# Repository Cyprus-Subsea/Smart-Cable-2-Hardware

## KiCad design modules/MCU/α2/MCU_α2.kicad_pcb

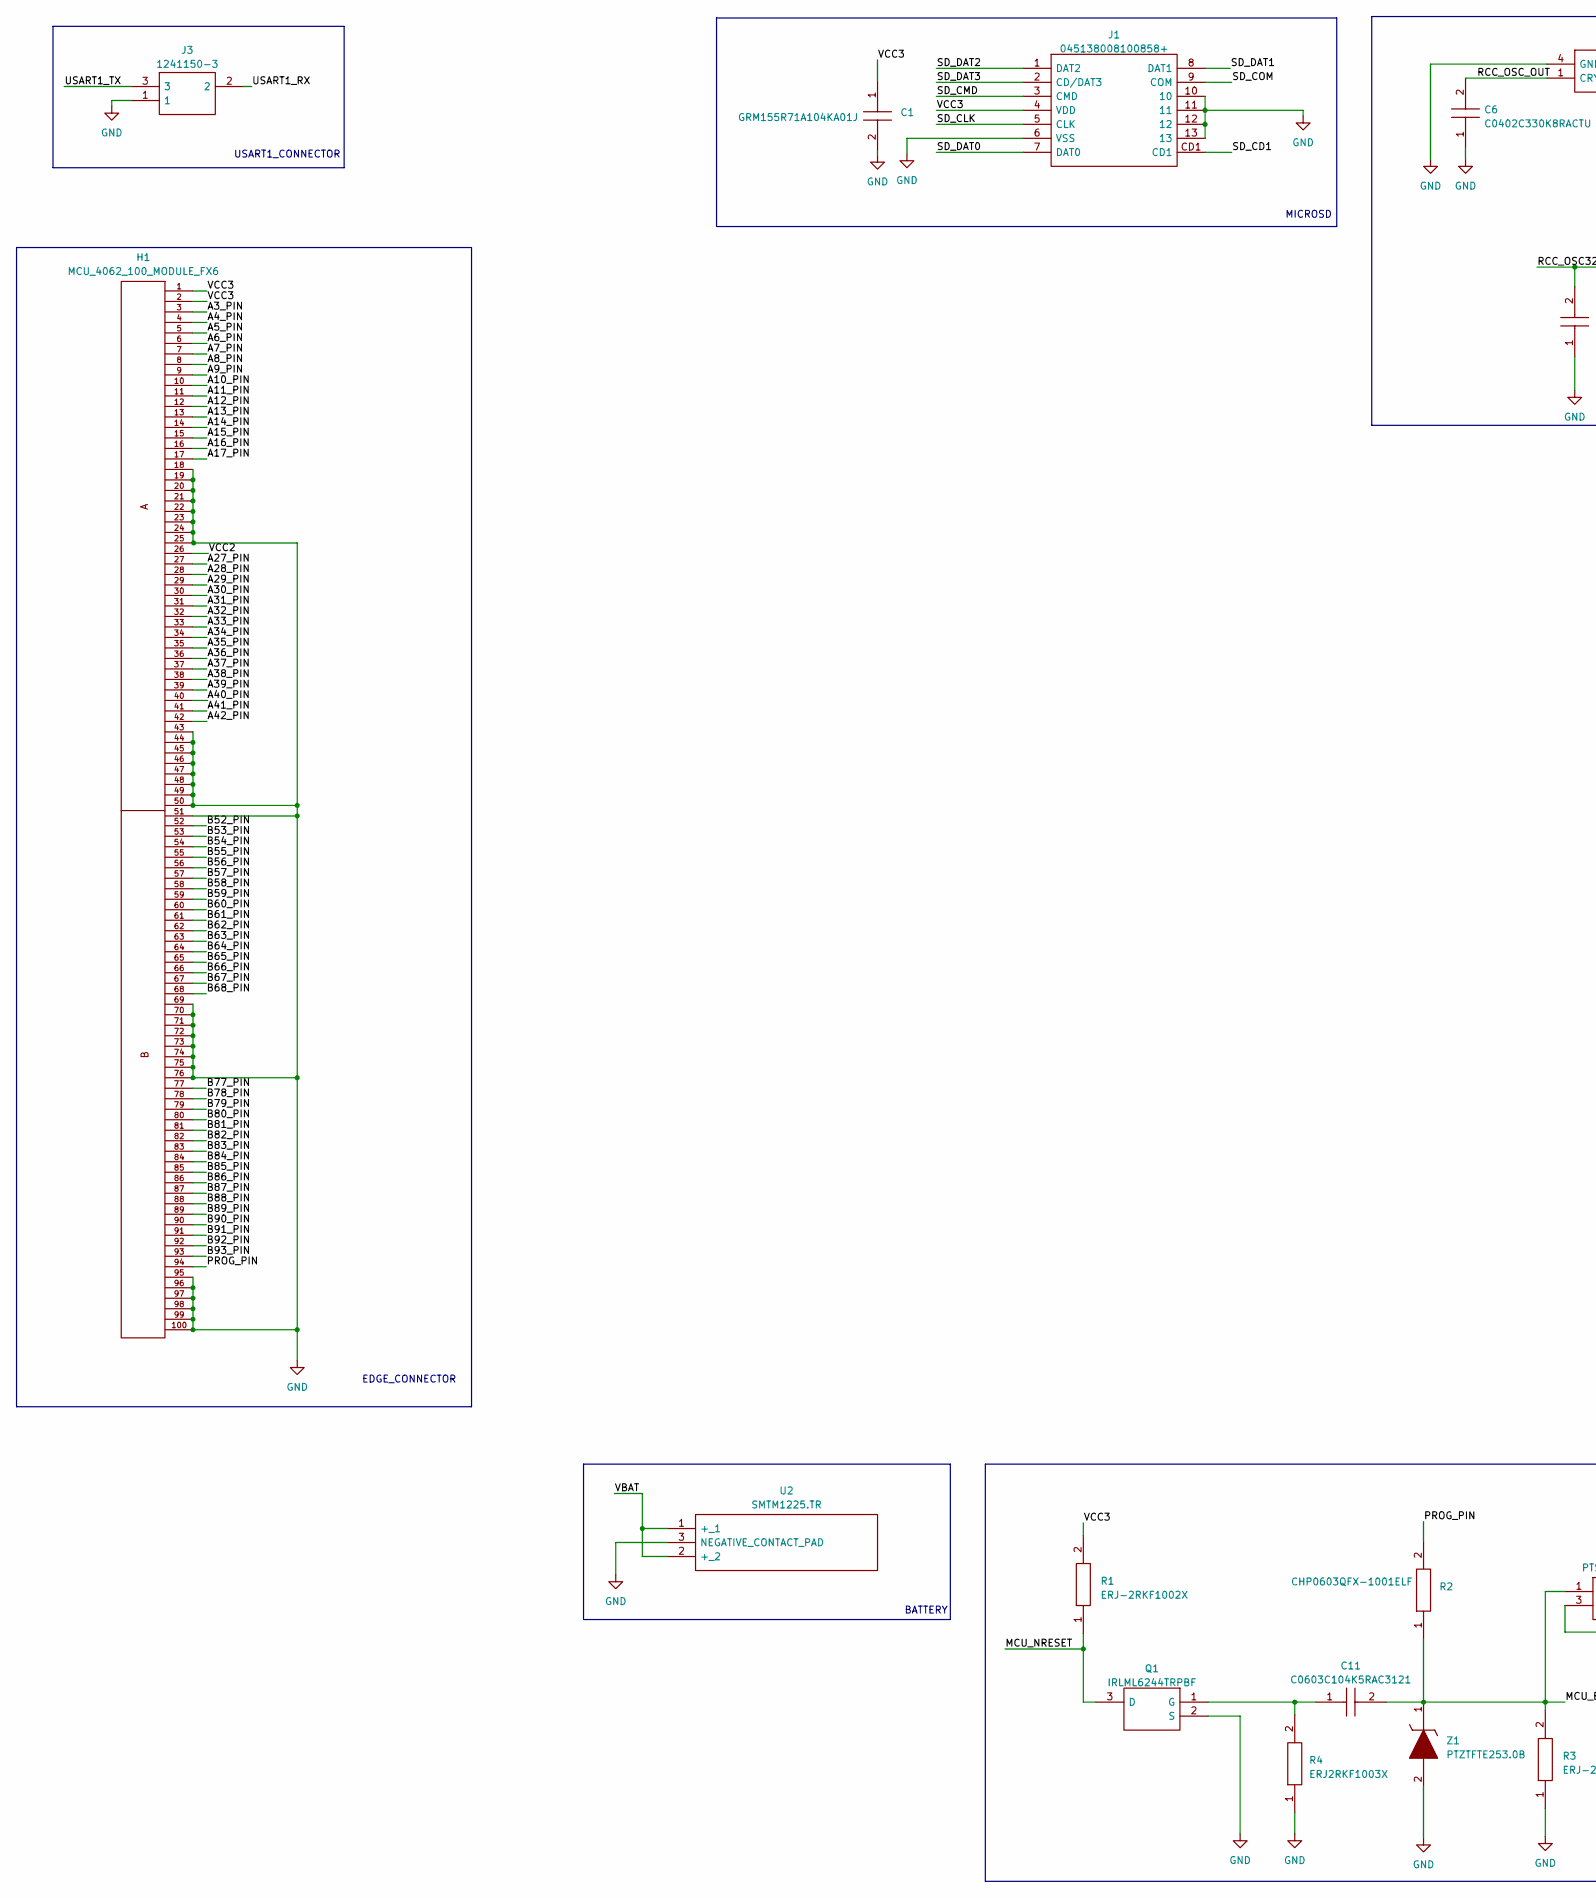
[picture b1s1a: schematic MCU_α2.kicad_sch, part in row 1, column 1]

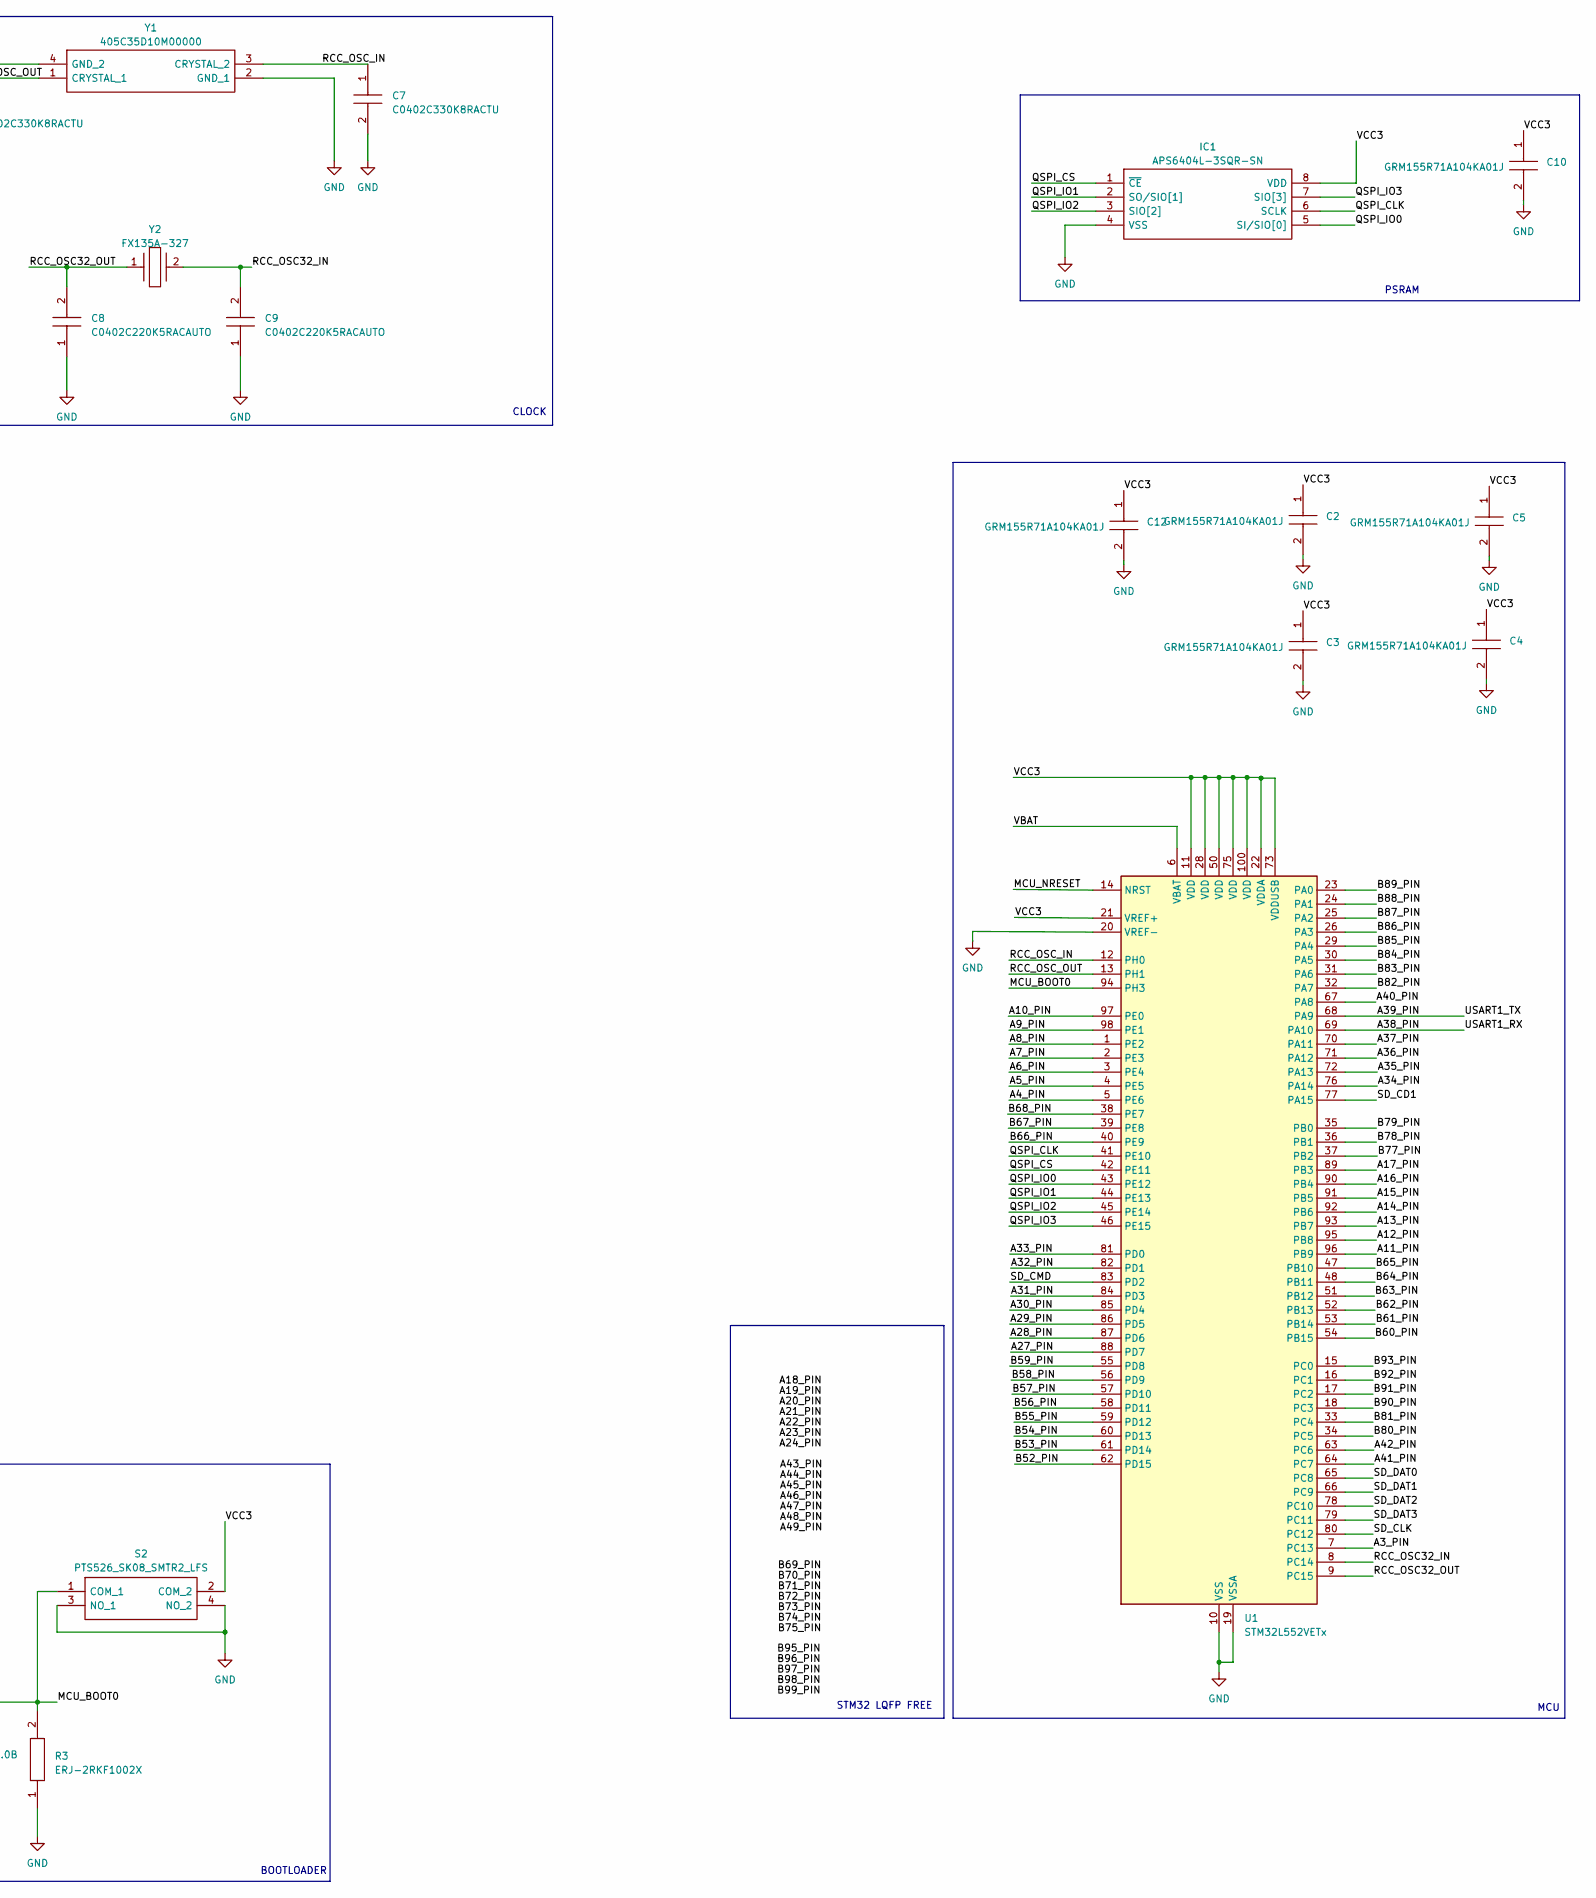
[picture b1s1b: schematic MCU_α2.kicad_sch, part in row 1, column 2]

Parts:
C1, C2, C3, C4, C5, C10, C12: GRM155R71A104KA01J; CAPC1005X55N; Manufacturer_Part_Number GRM155R71A104KA01J; Mouser Part Number 81-GRM155R71A104KA1J
C6, C7: C0402C330K8RACTU; CAPC1005X55N; Manufacturer_Part_Number C0402C330K8RACTU; Mouser Part Number 80-C0402C330K8RACTU
C8, C9: C0402C220K5RACAUTO; C0402; Manufacturer_Part_Number C0402C220K5RACAUTO; Mouser Part Number 80-C0402C220K5RAUTO
C11: C0603C104K5RAC3121; CAPC1608X95N; Manufacturer_Part_Number C0603C104K5RAC3121; Mouser Part Number 80-C603C104K5RAC3121
H1: MCU_4062_100_MODULE_FX6
IC1: APS6404L-3SQR-SN; SOIC127P600X175-8N; Manufacturer_Part_Number APS6404L-3SQR-SN; Mouser Part Number 878-APS6404L-3SQR-SN
J1: 045138008100858+; 045138008100858; Manufacturer_Part_Number 045138008100858+; Mouser Part Number 581-045138008100858+
J3: 1241150-3; 12411503; Manufacturer_Part_Number 1241150-3; Mouser Part Number 571-1241150-3
Q1: IRLML6244TRPBF; SOT95P237X112-3N; Manufacturer_Part_Number IRLML6244TRPBF; Mouser Part Number 942-IRLML6244TRPBF
R1, R3: ERJ-2RKF1002X; ERJ2RKD1004X; Manufacturer_Part_Number ERJ-2RKF1002X; Mouser Part Number 667-ERJ-2RKF1002X
R2: CHP0603QFX-1001ELF; RESC1608X55N; Manufacturer_Part_Number CHP0603QFX-1001ELF; Mouser Part Number 652-CHP0603QFX-1001E
R4: ERJ2RKF1003X; ERJ2RKD1004X; Manufacturer_Part_Number ERJ2RKF1003X
S2: PTS526_SK08_SMTR2_LFS; PTS526SKG15SMTR2LFS; Manufacturer_Part_Number PTS526 SK08 SMTR2 LFS; Mouser Part Number 611-PTS526SK08SMTR2L
U1: STM32L552VETx; LQFP-100_14x14mm_P0.5mm
U2: SMTM1225.TR; SMTM1225TR; Manufacturer_Part_Number SMTM1225.TR; Mouser Part Number 614-SMTM1225.TR
Y1: 405C35D10M00000; Manufacturer_Part_Number 405C35D10M00000; Mouser Part Number 774-405C35D10M00000
Y2: FX135A-327; FX135A327; Manufacturer_Part_Number FX135A-327
Z1: PTZTFTE253.0B; PTZTFTE2530B; Manufacturer_Part_Number PTZTFTE253.0B; Mouser Part Number 755-PTZTFTE253.0B

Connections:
/A3_PIN: H1.3, U1.7 (PC13)
/A4_PIN: H1.4, U1.5 (PE6)
/A5_PIN: H1.5, U1.4 (PE5)
/A6_PIN: H1.6, U1.3 (PE4)
/A7_PIN: H1.7, U1.2 (PE3)
/A8_PIN: H1.8, U1.1 (PE2)
/A9_PIN: H1.9, U1.98 (PE1)
/A10_PIN: H1.10, U1.97 (PE0)
/A11_PIN: H1.11, U1.96 (PB9)
/A12_PIN: H1.12, U1.95 (PB8)
/A13_PIN: H1.13, U1.93 (PB7)
/A14_PIN: H1.14, U1.92 (PB6)
/A15_PIN: H1.15, U1.91 (PB5)
/A16_PIN: H1.16, U1.90 (PB4)
/A17_PIN: H1.17, U1.89 (PB3)
/A27_PIN: H1.27, U1.88 (PD7)
/A28_PIN: H1.28, U1.87 (PD6)
/A29_PIN: H1.29, U1.86 (PD5)
/A30_PIN: H1.30, U1.85 (PD4)
/A31_PIN: H1.31, U1.84 (PD3)
/A32_PIN: H1.32, U1.82 (PD1)
/A33_PIN: H1.33, U1.81 (PD0)
/A34_PIN: H1.34, U1.76 (PA14)
/A35_PIN: H1.35, U1.72 (PA13)
/A36_PIN: H1.36, U1.71 (PA12)
/A37_PIN: H1.37, U1.70 (PA11)
/A38_PIN: H1.38, J3.2, U1.69 (PA10)
/A39_PIN: H1.39, J3.3, U1.68 (PA9)
/A40_PIN: H1.40, U1.67 (PA8)
/A41_PIN: H1.41, U1.64 (PC7)
/A42_PIN: H1.42, U1.63 (PC6)
/B52_PIN: H1.52, U1.62 (PD15)
/B53_PIN: H1.53, U1.61 (PD14)
/B54_PIN: H1.54, U1.60 (PD13)
/B55_PIN: H1.55, U1.59 (PD12)
/B56_PIN: H1.56, U1.58 (PD11)
/B57_PIN: H1.57, U1.57 (PD10)
/B58_PIN: H1.58, U1.56 (PD9)
/B59_PIN: H1.59, U1.55 (PD8)
/B60_PIN: H1.60, U1.54 (PB15)
/B61_PIN: H1.61, U1.53 (PB14)
/B62_PIN: H1.62, U1.52 (PB13)
/B63_PIN: H1.63, U1.51 (PB12)
/B64_PIN: H1.64, U1.48 (PB11)
/B65_PIN: H1.65, U1.47 (PB10)
/B66_PIN: H1.66, U1.40 (PE9)
/B67_PIN: H1.67, U1.39 (PE8)
/B68_PIN: H1.68, U1.38 (PE7)
/B77_PIN: H1.77, U1.37 (PB2)
/B78_PIN: H1.78, U1.36 (PB1)
/B79_PIN: H1.79, U1.35 (PB0)
/B80_PIN: H1.80, U1.34 (PC5)
/B81_PIN: H1.81, U1.33 (PC4)
/B82_PIN: H1.82, U1.32 (PA7)
/B83_PIN: H1.83, U1.31 (PA6)
/B84_PIN: H1.84, U1.30 (PA5)
/B85_PIN: H1.85, U1.29 (PA4)
/B86_PIN: H1.86, U1.26 (PA3)
/B87_PIN: H1.87, U1.25 (PA2)
/B88_PIN: H1.88, U1.24 (PA1)
/B89_PIN: H1.89, U1.23 (PA0)
/B90_PIN: H1.90, U1.18 (PC3)
/B91_PIN: H1.91, U1.17 (PC2)
/B92_PIN: H1.92, U1.16 (PC1)
/B93_PIN: H1.93, U1.15 (PC0)
/MCU_BOOT0: C11.2, R2.1, R3.2, S2.1 (COM_1), U1.94 (PH3), Z1.1
/MCU_NRESET: Q1.3 (D), R1.1, U1.14 (NRST)
/PROG_PIN: H1.94, R2.2
/QSPI_CLK: IC1.6 (SCLK), U1.41 (PE10)
/QSPI_CS: IC1.1 (~CE), U1.42 (PE11)
/QSPI_IO0: IC1.5 (SI/SIO[0]), U1.43 (PE12)
/QSPI_IO1: IC1.2 (SO/SIO[1]), U1.44 (PE13)
/QSPI_IO2: IC1.3 (SIO[2]), U1.45 (PE14)
/QSPI_IO3: IC1.7 (SIO[3]), U1.46 (PE15)
/RCC_OSC32_IN: C9.2, U1.8 (PC14), Y2.2
/RCC_OSC32_OUT: C8.2, U1.9 (PC15), Y2.1
/RCC_OSC_IN: C7.1, U1.12 (PH0), Y1.3 (CRYSTAL_2)
/RCC_OSC_OUT: C6.2, U1.13 (PH1), Y1.1 (CRYSTAL_1)
/SD_CD1: J1.CD1, U1.77 (PA15)
/SD_CLK: J1.5 (CLK), U1.80 (PC12)
/SD_CMD: J1.3 (CMD), U1.83 (PD2)
/SD_COM: J1.9 (COM)
/SD_DAT0: J1.7 (DAT0), U1.65 (PC8)
/SD_DAT1: J1.8 (DAT1), U1.66 (PC9)
/SD_DAT2: J1.1 (DAT2), U1.78 (PC10)
/SD_DAT3: J1.2 (CD/DAT3), U1.79 (PC11)
/VBAT: U1.6 (VBAT), U2.1 (+_1), U2.2 (+_2)
/VCC2: H1.26
/VCC3: C1.1, C2.1, C3.1, C4.1, C5.1, C10.1, C12.1, H1.1, H1.2, IC1.8 (VDD), J1.4 (VDD), R1.2, S2.2 (COM_2), U1.11 (VDD), U1.21 (VREF+), U1.22 (VDDA), U1.28 (VDD), U1.50 (VDD), U1.73 (VDDUSB), U1.75 (VDD), U1.100 (VDD)
GND: C1.2, C2.2, C3.2, C4.2, C5.2, C6.1, C7.2, C8.1, C9.1, C10.2, C12.2, H1.18, H1.19, H1.20, H1.21, H1.22, H1.23, H1.24, H1.25, H1.43, H1.44, H1.45, H1.46, H1.47, H1.48, H1.49, H1.50, H1.51, H1.69, H1.70, H1.71, H1.72, H1.73, H1.74, H1.75, H1.76, H1.95, H1.96, H1.97, H1.98, H1.99, H1.100, IC1.4 (VSS), J1.6 (VSS), J1.10, J1.11, J1.12, J1.13, J3.1, Q1.2 (S), R3.1, R4.1, S2.3 (NO_1), S2.4 (NO_2), U1.10 (VSS), U1.19 (VSSA), U1.20 (VREF-), U1.27 (VSS), U1.49 (VSS), U1.74 (VSS), U1.99 (VSS), U2.3 (NEGATIVE_CONTACT_PAD), Y1.2 (GND_1), Y1.4 (GND_2), Z1.2
unnamed: C11.1, Q1.1 (G), R4.2

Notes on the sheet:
EDGE_CONNECTOR
USART1_CONNECTOR
BOOTLOADER
CLOCK
STM32 LQFP FREE
MCU
BATTERY
MICROSD
PSRAM

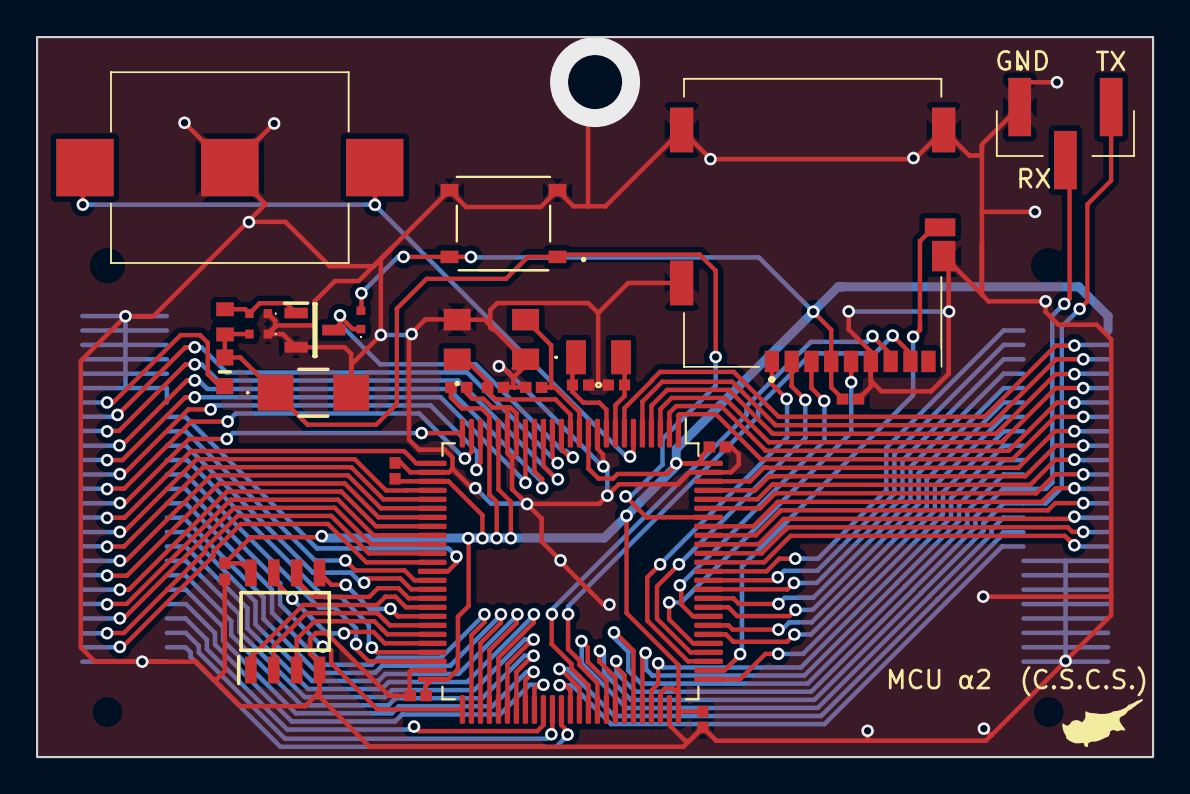
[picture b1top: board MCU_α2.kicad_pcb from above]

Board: 2 copper layers, 62.0 x 40.0 mm, 27 parts (1 on the bottom side), 89 nets.

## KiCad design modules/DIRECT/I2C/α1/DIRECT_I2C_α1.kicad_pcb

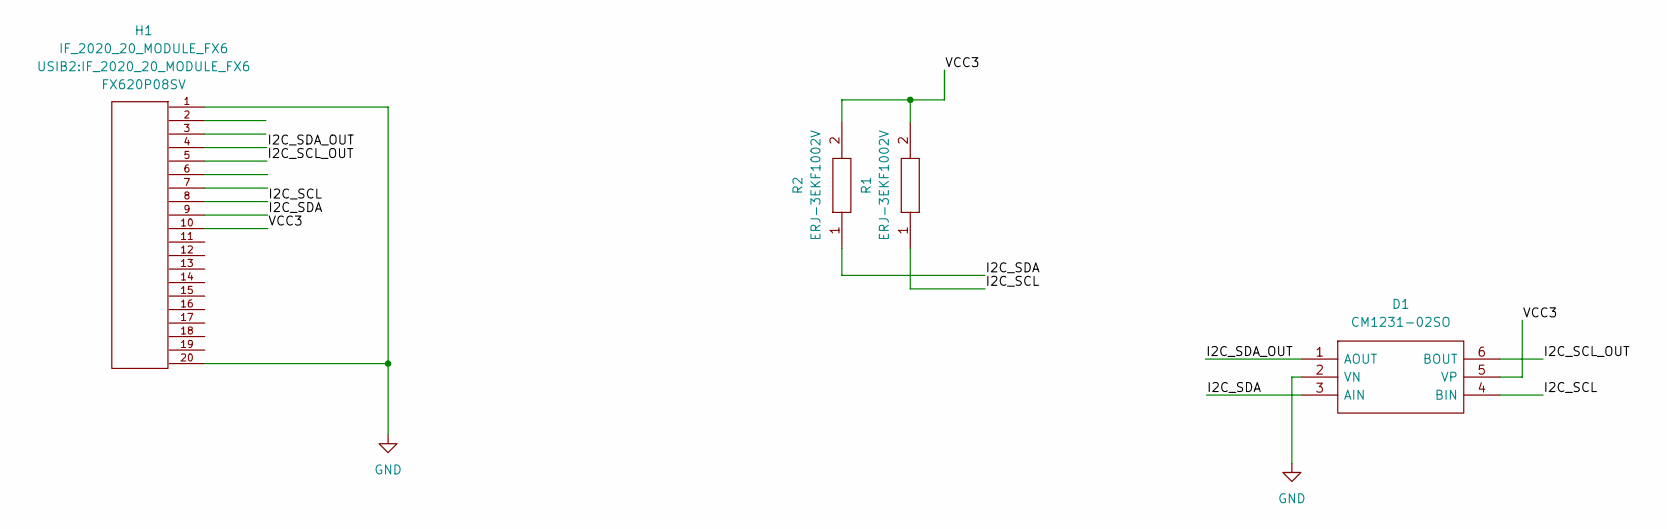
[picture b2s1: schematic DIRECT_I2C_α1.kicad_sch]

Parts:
D1: CM1231-02SO; SOT95P280X145-6N; Manufacturer_Part_Number CM1231-02SO; Mouser Part Number 748-CM1231-02SO
H1: IF_2020_20_MODULE_FX6
R1, R2: ERJ-3EKF1002V; ERJ3EK_(0603); Manufacturer_Part_Number ERJ-3EKF1002V; Mouser Part Number 667-ERJ-3EKF1002V

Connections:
/I2C_SCL: D1.4 (BIN), H1.8, R1.1
/I2C_SCL_OUT: D1.6 (BOUT), H1.5
/I2C_SDA: D1.3 (AIN), H1.9, R2.1
/I2C_SDA_OUT: D1.1 (AOUT), H1.4
/VCC3: D1.5 (VP), H1.10, R1.2, R2.2
GND: D1.2 (VN), H1.1, H1.20

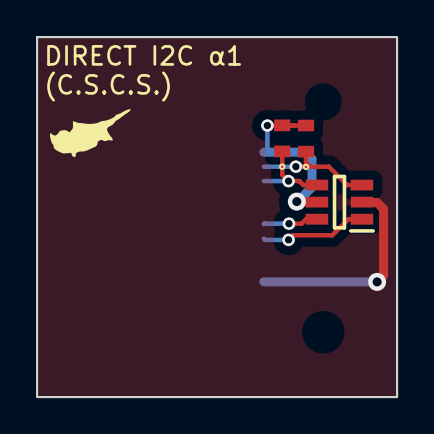
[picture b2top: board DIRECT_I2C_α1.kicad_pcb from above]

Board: 2 copper layers, 20.0 x 20.0 mm, 4 parts (1 on the bottom side), 6 nets.

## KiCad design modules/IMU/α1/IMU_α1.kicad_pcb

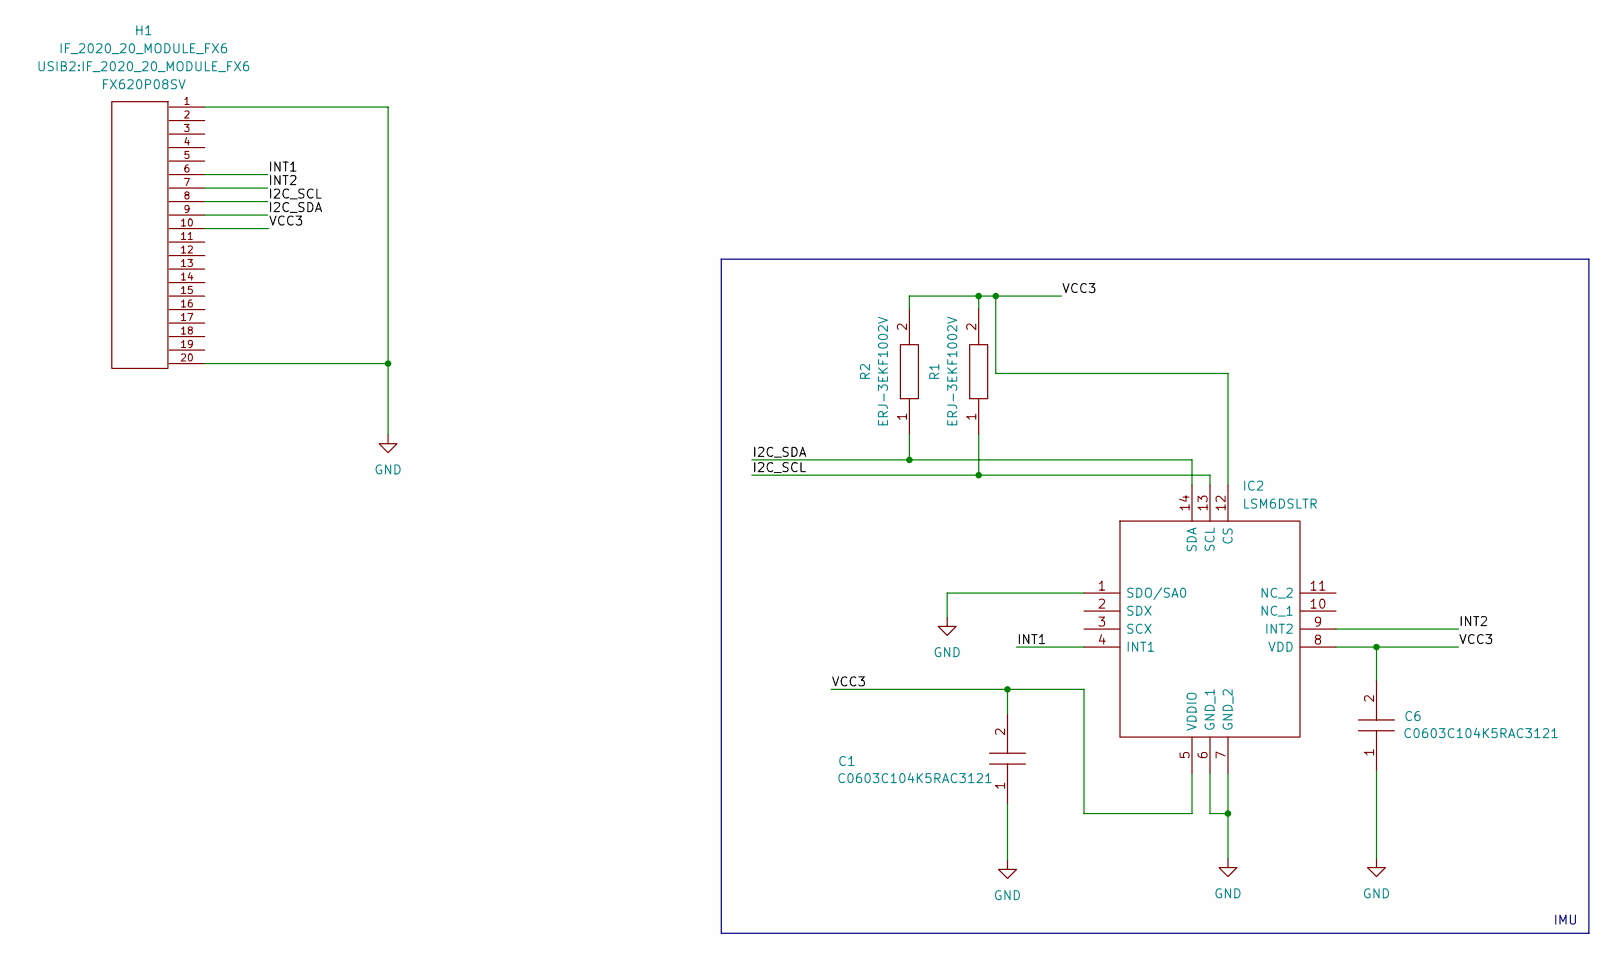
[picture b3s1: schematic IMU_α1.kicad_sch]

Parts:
C1, C6: C0603C104K5RAC3121; CAPC1608X95N; Manufacturer_Part_Number C0603C104K5RAC3121; Mouser Part Number 80-C603C104K5RAC3121
H1: IF_2020_20_MODULE_FX6
IC2: LSM6DSLTR; Manufacturer_Part_Number LSM6DSLTR; Mouser Part Number 511-LSM6DSLTR
R1, R2: ERJ-3EKF1002V; ERJ3EK_(0603); Manufacturer_Part_Number ERJ-3EKF1002V; Mouser Part Number 667-ERJ-3EKF1002V

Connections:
/I2C_SCL: H1.8, IC2.13 (SCL), R1.1
/I2C_SDA: H1.9, IC2.14 (SDA), R2.1
/INT1: H1.6, IC2.4 (INT1)
/INT2: H1.7, IC2.9 (INT2)
/VCC3: C1.2, C6.2, H1.10, IC2.5 (VDDIO), IC2.8 (VDD), IC2.12 (CS), R1.2, R2.2
GND: C1.1, C6.1, H1.1, H1.20, IC2.1 (SDO/SA0), IC2.6 (GND_1), IC2.7 (GND_2)

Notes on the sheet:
IMU

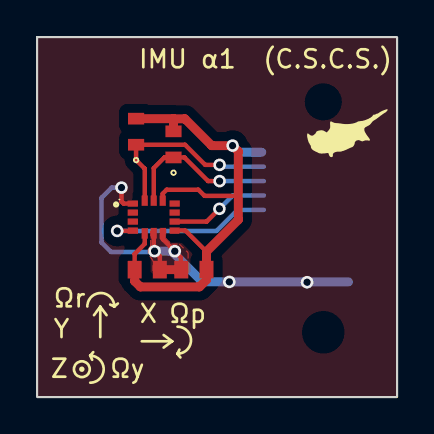
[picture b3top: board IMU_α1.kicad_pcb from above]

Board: 2 copper layers, 20.0 x 20.0 mm, 6 parts (1 on the bottom side), 6 nets.

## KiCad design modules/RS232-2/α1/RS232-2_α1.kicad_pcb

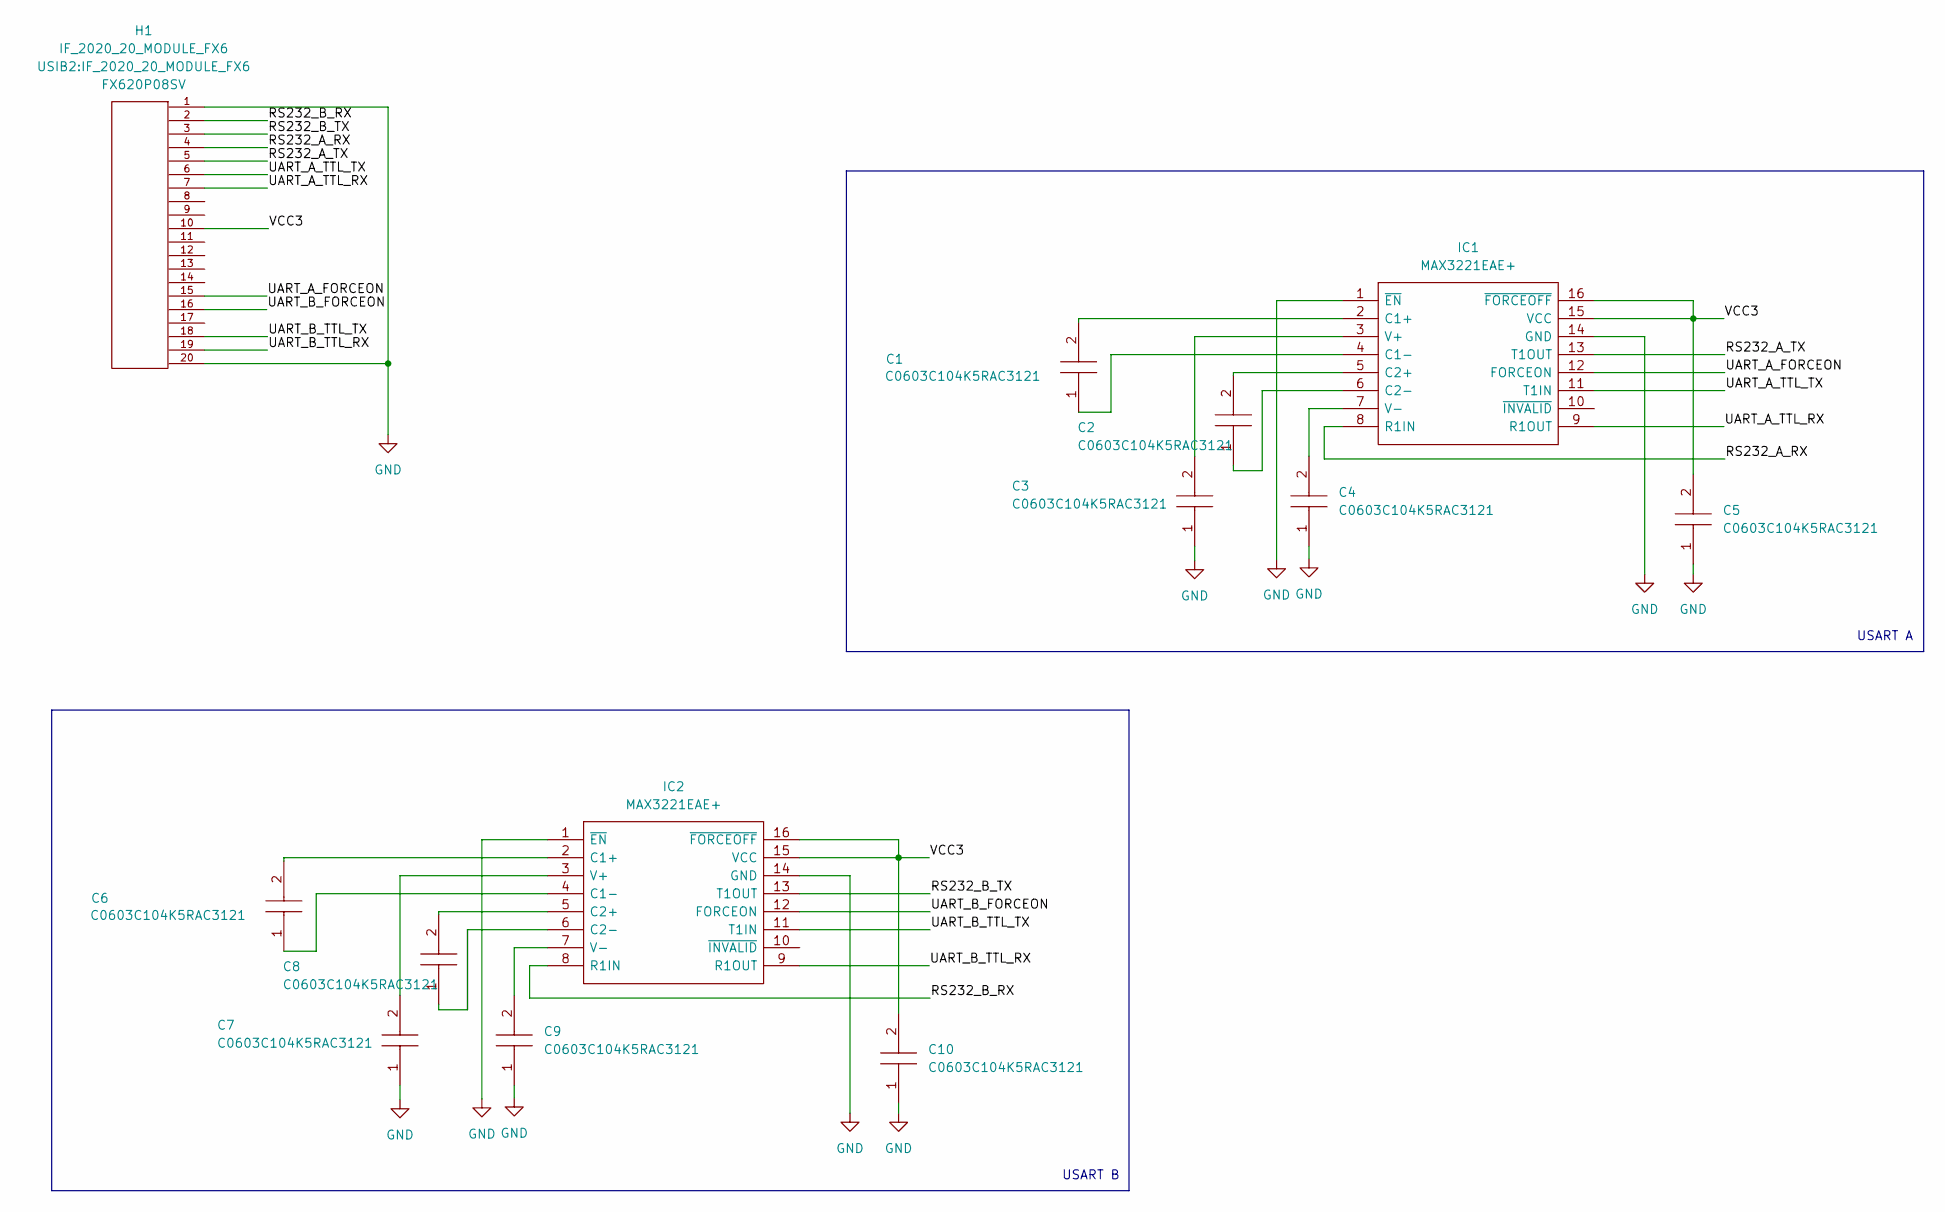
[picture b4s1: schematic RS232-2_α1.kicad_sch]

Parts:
C1, C2, C3, C4, C5, C6, C7, C8, C9, C10: C0603C104K5RAC3121; CAPC1608X95N; Manufacturer_Part_Number C0603C104K5RAC3121; Mouser Part Number 80-C603C104K5RAC3121
H1: IF_2020_20_MODULE_FX6
IC1, IC2: MAX3221EAE+; SOP65P778X199-16N; Manufacturer_Part_Number MAX3221EAE+; Mouser Part Number 700-MAX3221EAE

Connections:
/RS232_A_RX: H1.4, IC1.8 (R1IN)
/RS232_A_TX: H1.5, IC1.13 (T1OUT)
/RS232_B_RX: H1.2, IC2.8 (R1IN)
/RS232_B_TX: H1.3, IC2.13 (T1OUT)
/UART_A_FORCEON: H1.15, IC1.12 (FORCEON)
/UART_A_TTL_RX: H1.7, IC1.9 (R1OUT)
/UART_A_TTL_TX: H1.6, IC1.11 (T1IN)
/UART_B_FORCEON: H1.16, IC2.12 (FORCEON)
/UART_B_TTL_RX: H1.19, IC2.9 (R1OUT)
/UART_B_TTL_TX: H1.18, IC2.11 (T1IN)
/VCC3: C5.2, C10.2, H1.10, IC1.15 (VCC), IC1.16 (~FORCEOFF), IC2.15 (VCC), IC2.16 (~FORCEOFF)
GND: C3.1, C4.1, C5.1, C7.1, C9.1, C10.1, H1.1, H1.20, IC1.1 (~EN), IC1.14 (GND), IC2.1 (~EN), IC2.14 (GND)
unnamed: C1.2, IC1.2 (C1+)
unnamed: C1.1, IC1.4 (C1-)
unnamed: C2.2, IC1.5 (C2+)
unnamed: C2.1, IC1.6 (C2-)
unnamed: C3.2, IC1.3 (V+)
unnamed: C4.2, IC1.7 (V-)
unnamed: C6.2, IC2.2 (C1+)
unnamed: C6.1, IC2.4 (C1-)
unnamed: C8.2, IC2.5 (C2+)
unnamed: C8.1, IC2.6 (C2-)
unnamed: C7.2, IC2.3 (V+)
unnamed: C9.2, IC2.7 (V-)

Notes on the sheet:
USART A
USART B

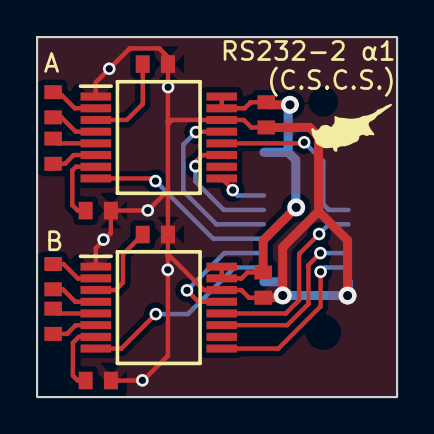
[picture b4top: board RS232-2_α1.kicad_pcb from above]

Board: 2 copper layers, 20.0 x 20.0 mm, 13 parts (1 on the bottom side), 24 nets.

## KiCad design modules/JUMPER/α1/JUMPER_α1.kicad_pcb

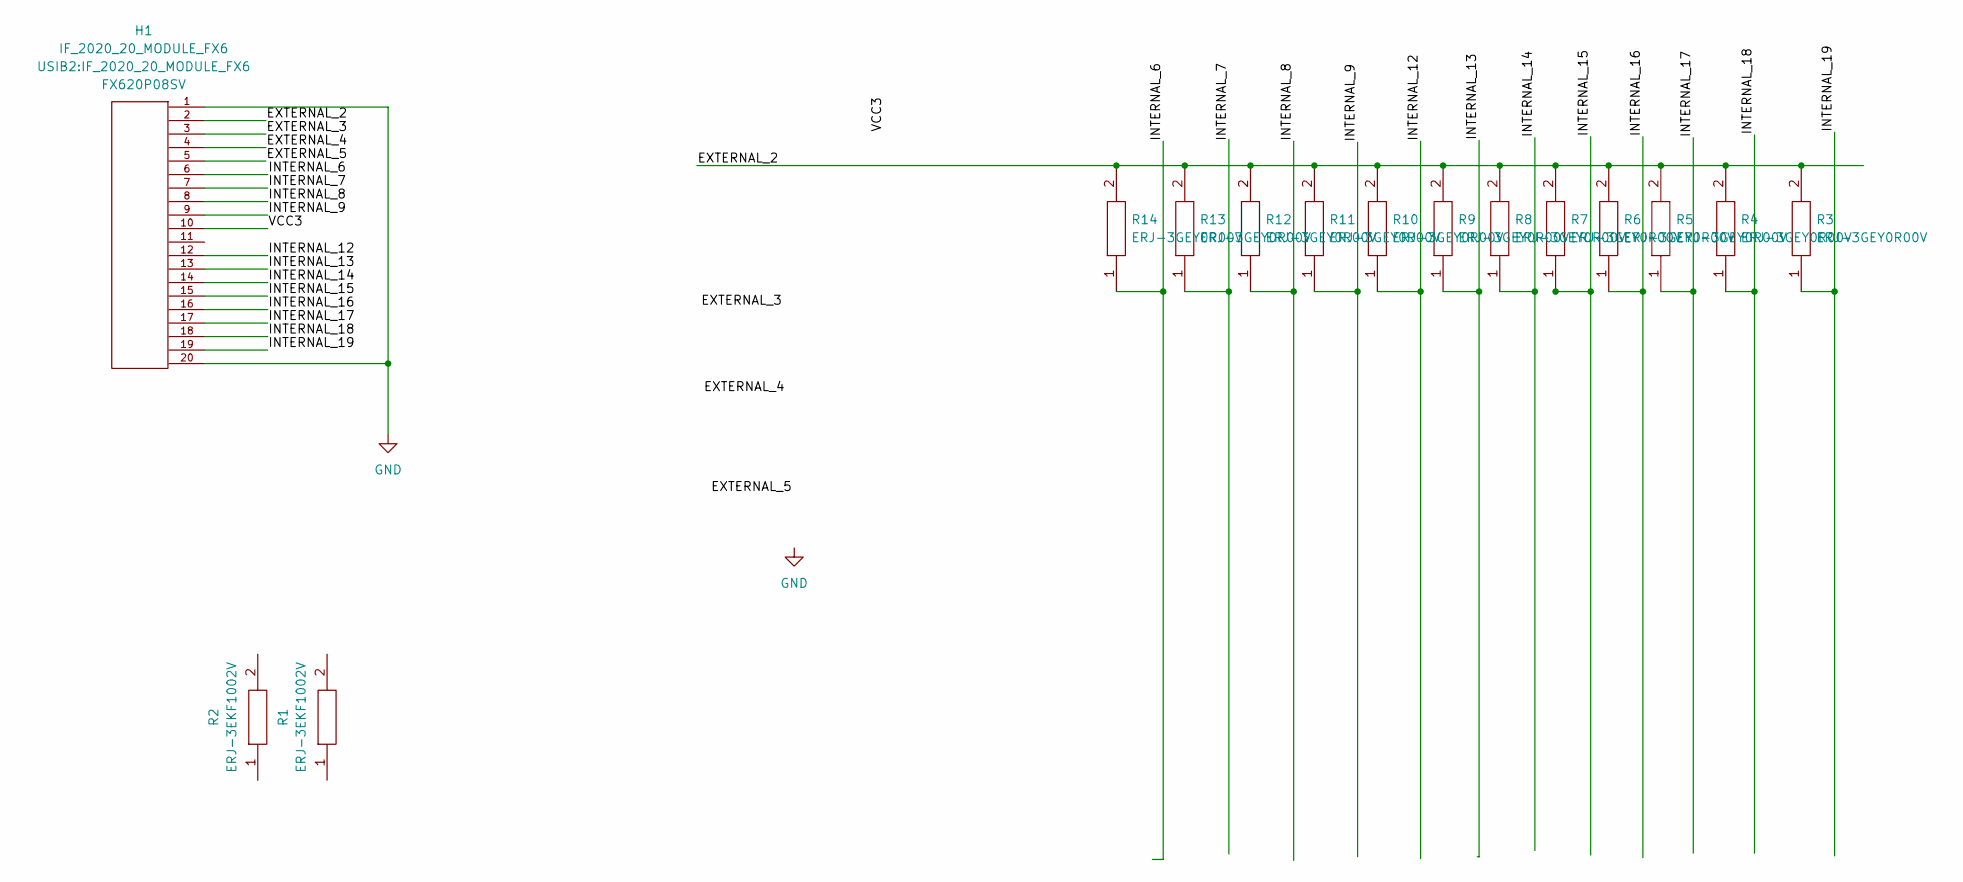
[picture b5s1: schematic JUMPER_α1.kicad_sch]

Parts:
H1: IF_2020_20_MODULE_FX6
R1, R2: ERJ-3EKF1002V; ERJ3EK_(0603); Manufacturer_Part_Number ERJ-3EKF1002V; Mouser Part Number 667-ERJ-3EKF1002V
R3, R4, R5, R6, R7, R8, R9, R10, R11, R12, R13, R14: ERJ-3GEY0R00V; ERJ3EKF1000V; Manufacturer_Part_Number ERJ-3GEY0R00V; Mouser Part Number 667-ERJ-3GEY0R00V

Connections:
/EXTERNAL_2: H1.2, R3.2, R4.2, R5.2, R6.2, R7.2, R8.2, R9.2, R10.2, R11.2, R12.2, R13.2, R14.2
/EXTERNAL_3: H1.3
/EXTERNAL_4: H1.4
/EXTERNAL_5: H1.5
/INTERNAL_6: H1.6, R14.1
/INTERNAL_7: H1.7, R13.1
/INTERNAL_8: H1.8, R12.1
/INTERNAL_9: H1.9, R11.1
/INTERNAL_12: H1.12, R10.1
/INTERNAL_13: H1.13, R9.1
/INTERNAL_14: H1.14, R8.1
/INTERNAL_15: H1.15, R7.1
/INTERNAL_16: H1.16, R6.1
/INTERNAL_17: H1.17, R5.1
/INTERNAL_18: H1.18, R4.1
/INTERNAL_19: H1.19, R3.1
/VCC3: H1.10
GND: H1.1, H1.20

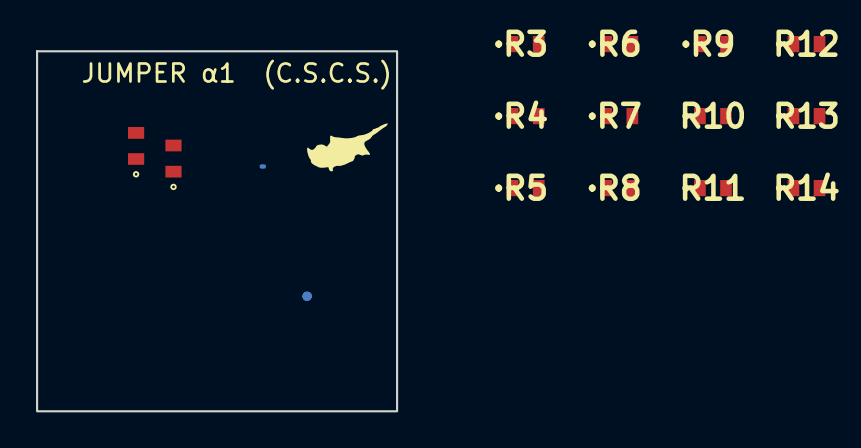
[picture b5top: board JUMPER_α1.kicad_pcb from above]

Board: 2 copper layers, 20.0 x 20.0 mm, 15 parts (1 on the bottom side), 14 nets.
